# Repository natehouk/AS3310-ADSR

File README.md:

# SS-ADSR-1
Envelope generator based on the AS3310-ADSR.

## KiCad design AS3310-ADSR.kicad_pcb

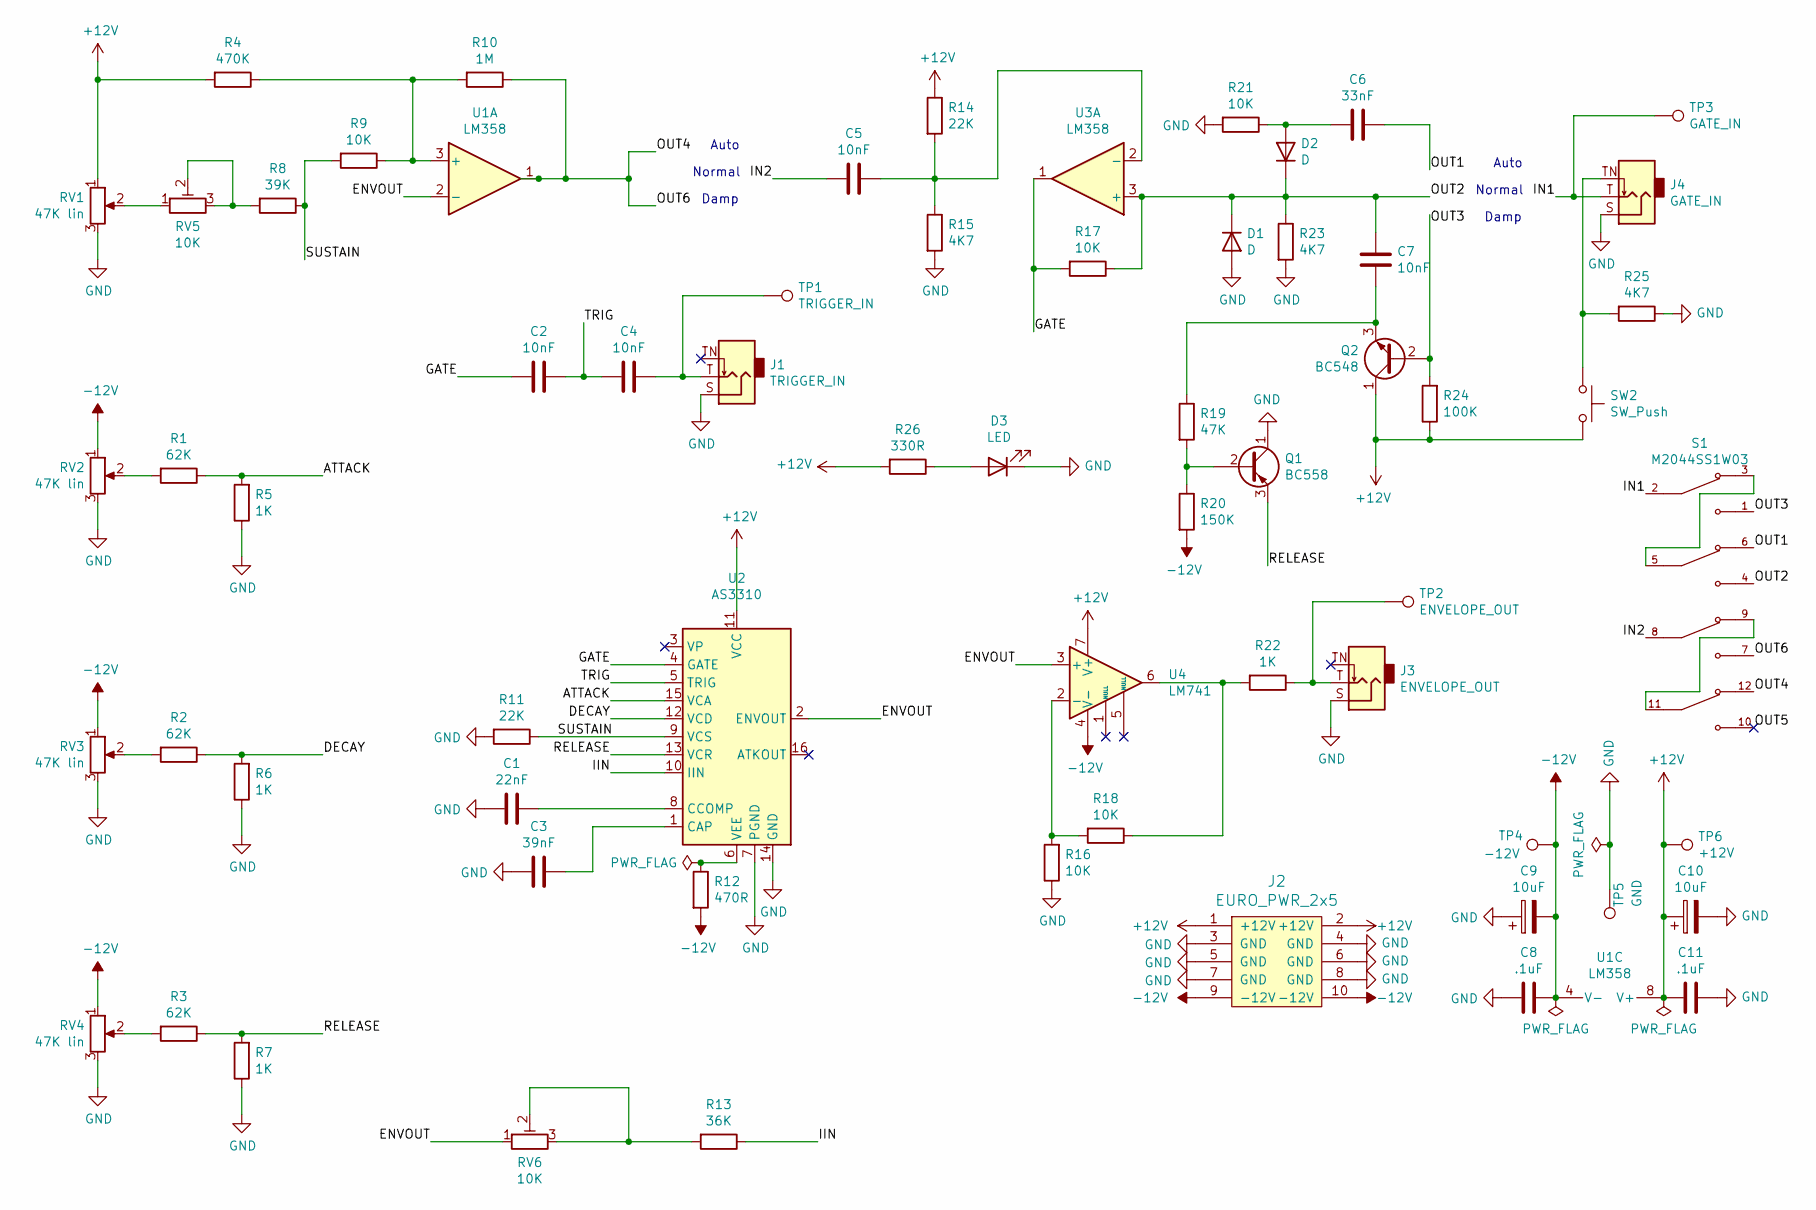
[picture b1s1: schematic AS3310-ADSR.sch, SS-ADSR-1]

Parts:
C1: 22nF; C_Disc_D7.5mm_W2.5mm_P5.00mm
C2, C4, C5, C7: 10nF; C_Disc_D7.5mm_W2.5mm_P5.00mm
C3: 39nF; C_Disc_D7.5mm_W2.5mm_P5.00mm
C6: 33nF; C_Disc_D7.5mm_W2.5mm_P5.00mm
C8, C11: .1uF; C_Disc_D7.5mm_W2.5mm_P5.00mm
C9, C10: 10uF; CP_Radial_D5.0mm_P2.50mm
D1, D2: D; D_DO-35_SOD27_P7.62mm_Horizontal
D3: LED; LED_D5.0mm
J1: TRIGGER_IN; Jack_3.5mm_QingPu_WQP-PJ398SM_Vertical_CircularHoles
J2: EURO_PWR_2x5; PinHeader_2x05_P2.54mm_Vertical
J3: ENVELOPE_OUT; Jack_3.5mm_QingPu_WQP-PJ398SM_Vertical_CircularHoles
J4: GATE_IN; Jack_3.5mm_QingPu_WQP-PJ398SM_Vertical_CircularHoles
Q1: BC558; TO-92_Inline
Q2: BC548; TO-92_Inline
R1, R2, R3: 62K; R_Axial_DIN0207_L6.3mm_D2.5mm_P10.16mm_Horizontal
R4: 470K; R_Axial_DIN0207_L6.3mm_D2.5mm_P10.16mm_Horizontal
R5, R6, R7, R22: 1K; R_Axial_DIN0207_L6.3mm_D2.5mm_P10.16mm_Horizontal
R8: 39K; R_Axial_DIN0207_L6.3mm_D2.5mm_P10.16mm_Horizontal
R9, R16, R17, R18, R21: 10K; R_Axial_DIN0207_L6.3mm_D2.5mm_P10.16mm_Horizontal
R10: 1M; R_Axial_DIN0207_L6.3mm_D2.5mm_P10.16mm_Horizontal
R11, R14: 22K; R_Axial_DIN0207_L6.3mm_D2.5mm_P10.16mm_Horizontal
R12: 470R; R_Axial_DIN0207_L6.3mm_D2.5mm_P10.16mm_Horizontal
R13: 36K; R_Axial_DIN0207_L6.3mm_D2.5mm_P10.16mm_Horizontal
R15, R23, R25: 4K7; R_Axial_DIN0207_L6.3mm_D2.5mm_P10.16mm_Horizontal
R19: 47K; R_Axial_DIN0207_L6.3mm_D2.5mm_P10.16mm_Horizontal
R20: 150K; R_Axial_DIN0207_L6.3mm_D2.5mm_P10.16mm_Horizontal
R24: 100K; R_Axial_DIN0207_L6.3mm_D2.5mm_P10.16mm_Horizontal
R26: 330R; R_Axial_DIN0207_L6.3mm_D2.5mm_P10.16mm_Horizontal
RV1, RV2, RV3, RV4: 47K lin; Potentiometer_Alpha_RD901F-40-00D_Single_Vertical
RV5, RV6: 10K; TRIM_3266W-1-102LF
S1: M2044SS1W03; SW_M2044SS1W03
SW2: SW_Push; SW_PS1024ALRED
TP1: TRIGGER_IN; TestPoint_Pad_4.0x4.0mm
TP2: ENVELOPE_OUT; TestPoint_Pad_4.0x4.0mm
TP3: GATE_IN; TestPoint_Pad_4.0x4.0mm
TP4: -12V; TestPoint_Pad_4.0x4.0mm
TP5: GND; TestPoint_Pad_4.0x4.0mm
TP6: +12V; TestPoint_Pad_4.0x4.0mm
U1, U3: LM358; DIP-8_W7.62mm
U2: AS3310; DIP-16_W7.62mm
U4: LM741; DIP-8_W7.62mm

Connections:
+12V: C10.1, C11.2, J2.1 (+12V), J2.2 (+12V), Q2.1 (C), R4.2, R14.1, R24.1, R26.2, RV1.1, SW2.2, TP6.1, U1.8 (V+), U2.11 (VCC), U4.7 (V+)
-12V: C8.1, C9.2, J2.9 (-12V), J2.10 (-12V), R12.2, R20.2, RV2.1, RV3.1, RV4.1, TP4.1, U1.4 (V-), U4.4 (V-)
/ATTACK: R1.1, R5.2, U2.15 (VCA)
/DECAY: R2.1, R6.2, U2.12 (VCD)
/ENVOUT: RV6.1, U1.2 (-), U2.2 (ENVOUT), U4.3 (+)
/GATE: C2.2, R17.2, U2.4 (GATE), U3.1
/IIN: R13.1, U2.10 (IIN)
/IN1: J4.T, S1.2, TP3.1
/IN2: C5.2, S1.8
/OUT1: C6.1, S1.6
/OUT2: C7.1, D1.1 (K), D2.1 (K), R17.1, R23.1, S1.4, U3.3 (+)
/OUT3: Q2.2 (B), R24.2, S1.1
/OUT4: R10.1, S1.7, S1.12, U1.1
/RELEASE: Q1.3 (E), R3.1, R7.2, U2.13 (VCR)
/SUSTAIN: R8.1, R9.2, R11.1, U2.9 (VCS)
/TRIG: C2.1, C4.2, U2.5 (TRIG)
GND: C1.2, C3.2, C8.2, C9.1, C10.2, C11.1, D1.2 (A), D3.1 (K), J1.S, J2.3 (GND), J2.4 (GND), J2.5 (GND), J2.6 (GND), J2.7 (GND), J2.8 (GND), J3.S, J4.S, Q1.1 (C), R5.1, R6.1, R7.1, R11.2, R15.2, R16.1, R21.2, R23.2, R25.1, RV1.3, RV2.3, RV3.3, RV4.3, TP5.1, U2.7 (PGND), U2.14 (GND)
unnamed: C1.1, U2.8 (CCOMP)
unnamed: C3.1, U2.1 (CAP)
unnamed: C4.1, J1.T, TP1.1
unnamed: C5.1, R14.2, R15.1, U3.2 (-)
unnamed: C6.2, D2.2 (A), R21.1
unnamed: C7.2, Q2.3 (E), R19.1
unnamed: D3.2 (A), R26.1
unnamed: J3.T, R22.1, TP2.1
unnamed: J4.TN, R25.2, SW2.1
unnamed: Q1.2 (B), R19.2, R20.1
unnamed: R1.2, RV2.2
unnamed: R2.2, RV3.2
unnamed: R3.2, RV4.2
unnamed: R8.2, RV5.2, RV5.3
unnamed: R4.1, R9.1, R10.2, U1.3 (+)
unnamed: R12.1, U2.6 (VEE)
unnamed: R13.2, RV6.2, RV6.3
unnamed: R16.2, R18.2, U4.2 (-)
unnamed: R18.1, R22.2, U4.6
unnamed: RV1.2, RV5.1
unnamed: S1.3, S1.5
unnamed: S1.9, S1.11

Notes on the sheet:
Auto
Normal
Damp

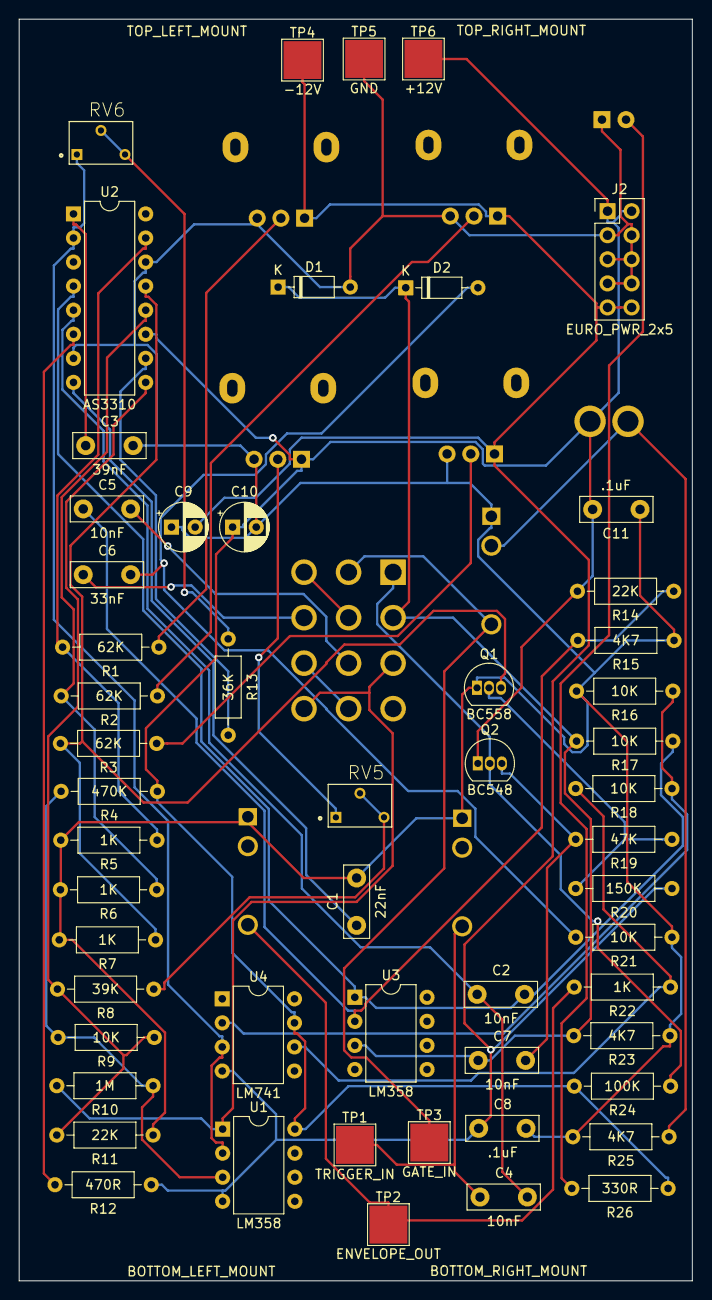
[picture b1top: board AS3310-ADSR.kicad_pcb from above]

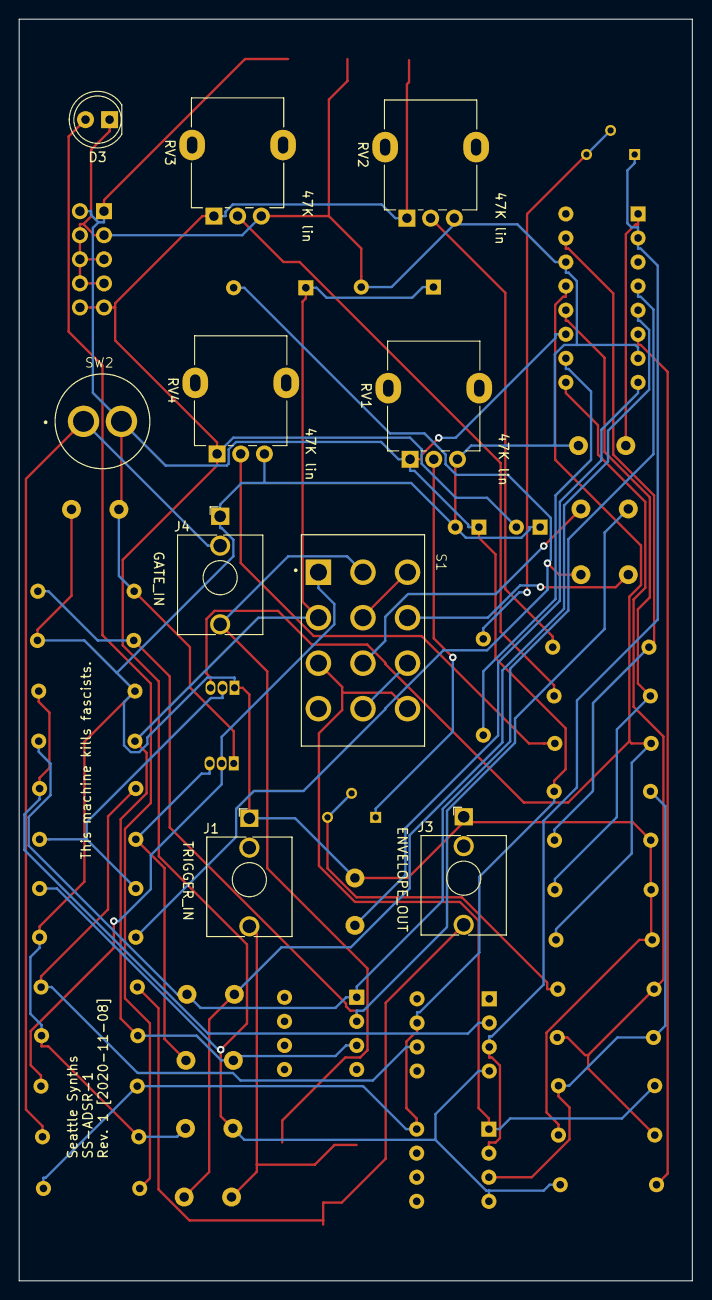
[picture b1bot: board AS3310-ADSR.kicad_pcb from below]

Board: 2 copper layers, 71.0 x 133.1 mm, 68 parts (10 on the bottom side), 39 nets.

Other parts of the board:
BOTTOM_LEFT_MOUNT: MountingHole_3.2mm_M3_Oval
BOTTOM_RIGHT_MOUNT: MountingHole_3.2mm_M3_Oval
TOP_LEFT_MOUNT: MountingHole_3.2mm_M3_Oval
TOP_RIGHT_MOUNT: MountingHole_3.2mm_M3_Oval

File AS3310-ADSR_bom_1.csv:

Component,Description,Part,References,Value,Footprint,Quantity Per PCB,Datasheet,Field4,Field5,Field6
1,Unpolarized capacitor,C,C2 C4 C5 C7,10nF,C_Disc_D7.5mm_W2.5mm_P5.00mm,4,~,,,
2,Unpolarized capacitor,C,C1,22nF,C_Disc_D7.5mm_W2.5mm_P5.00mm,1,~,,,
3,Unpolarized capacitor,C,C6,33nF,C_Disc_D7.5mm_W2.5mm_P5.00mm,1,~,,,
4,Unpolarized capacitor,C,C3,39nF,C_Disc_D7.5mm_W2.5mm_P5.00mm,1,~,,,
5,Unpolarized capacitor,C,C8 C11,.1uF,C_Disc_D7.5mm_W2.5mm_P5.00mm,2,~,,,
6,Unpolarized capacitor,C,C9 C10,10uF,C_Disc_D7.5mm_W2.5mm_P5.00mm,2,~,,,
7,Diode,D,D1 D2,D,D_DO-35_SOD27_P7.62mm_Horizontal,2,~,,,
8,Light emitting diode,LED,D3,LED,LED_D5.0mm,1,~,,,
9,,EURO_PWR_2x5,J2,EURO_PWR_2x5,PinHeader_2x05_P2.54mm_Vertical,1,,,,
10,"Audio Jack, 2 Poles (Mono / TS), Switched T Pole (Normalling)",AudioJack2_SwitchT,J1 J3 J4,TRIGGER_IN,Jack_3.5mm_QingPu_WQP-PJ398SM_Vertical_CircularHoles,3,~,,,
11,"0.1A Ic, 30V Vce, Small Signal NPN Transistor, TO-92",BC548,Q2,BC548,TO-92_Inline,1,https://www.onsemi.com/pub/Collateral/BC550-D.pdf,,,
12,"0.1A Ic, 30V Vce, PNP Small Signal Transistor, TO-92",BC558,Q1,BC558,TO-92_Inline,1,https://www.onsemi.com/pub/Collateral/BC556BTA-D.pdf,,,
13,Resistor,R,R26,330R,R_Axial_DIN0207_L6.3mm_D2.5mm_P10.16mm_Horizontal,1,~,,,
14,Resistor,R,R12,470R,R_Axial_DIN0207_L6.3mm_D2.5mm_P10.16mm_Horizontal,1,~,,,
15,Resistor,R,R5 R6 R7 R22,1K,R_Axial_DIN0207_L6.3mm_D2.5mm_P10.16mm_Horizontal,4,~,,,
16,Resistor,R,R15 R23 R25,4K7,R_Axial_DIN0207_L6.3mm_D2.5mm_P10.16mm_Horizontal,3,~,,,
17,Resistor,R,R9 R16 R17 R18 R21,10K,R_Axial_DIN0207_L6.3mm_D2.5mm_P10.16mm_Horizontal,5,~,,,
18,Resistor,R,R11 R14,22K,R_Axial_DIN0207_L6.3mm_D2.5mm_P10.16mm_Horizontal,2,~,,,
19,Resistor,R,R13,36K,R_Axial_DIN0207_L6.3mm_D2.5mm_P10.16mm_Horizontal,1,~,,,
20,Resistor,R,R8,39K,R_Axial_DIN0207_L6.3mm_D2.5mm_P10.16mm_Horizontal,1,~,,,
21,Resistor,R,R19,47K,R_Axial_DIN0207_L6.3mm_D2.5mm_P10.16mm_Horizontal,1,~,,,
22,Resistor,R,R1 R2 R3,62K,R_Axial_DIN0207_L6.3mm_D2.5mm_P10.16mm_Horizontal,3,~,,,
23,Resistor,R,R24,100K,R_Axial_DIN0207_L6.3mm_D2.5mm_P10.16mm_Horizontal,1,~,,,
24,Resistor,R,R20,150K,R_Axial_DIN0207_L6.3mm_D2.5mm_P10.16mm_Horizontal,1,~,,,
25,Resistor,R,R4,470K,R_Axial_DIN0207_L6.3mm_D2.5mm_P10.16mm_Horizontal,1,~,,,
26,Resistor,R,R10,1M,R_Axial_DIN0207_L6.3mm_D2.5mm_P10.16mm_Horizontal,1,~,,,
27,Trim-potentiometer,R_Potentiometer_Trim,RV5 RV6,10K,Potentiometer_Runtron_RM-065_Vertical,2,~,,,
28,Potentiometer,R_Potentiometer,RV1 RV2 RV3 RV4,47K lin,Potentiometer_Alpha_RD901F-40-00D_Single_Vertical,4,~,,,
29,,M2044SS1W03,S1,M2044SS1W03,SW_M2044SS1W03,1,30.9 mm,NKK Switches,5/9/18,Manufacturer Recommendations
30,"Push button switch, generic, two pins",SW_Push,SW2,SW_Push,SW_PUSH_6mm_H5mm,1,~,,,
31,"ADSR Voltage Controlled Envelope Generator, DIP-16/SOIC-16",AS3310,U2,AS3310,DIP-16_W7.62mm,1,http://www.alfarzpp.lv/eng/sc/AS3310.pdf,,,
32,"Low-Power, Dual Operational Amplifiers, DIP-8/SOIC-8/TO-99-8",LM358,U1 U3,LM358,DIP-8_W7.62mm,2,http://www.ti.com/lit/ds/symlink/lm2904-n.pdf,,,
33,"Operational Amplifier, DIP-8/TO-99-8",LM741,U4,LM741,DIP-8_W7.62mm,1,http://www.ti.com/lit/ds/symlink/lm741.pdf,,,





Component Groups:,33
Component Count:,58
Fitted Components:,58
Number of PCBs:,1
Total components:,58
Schematic Version:,1
Schematic Date:,2020-11-01
PCB Variant:,default
BoM Date:,Sun 08 Nov 2020 06:55:45 PM CET
Schematic Source:,AS3310-ADSR.sch
KiCad Version:,Eeschema 5.1.7

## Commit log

2020-11-01 Fix typo.
2020-11-01 Refactor
2020-11-02 Add Eurocad symbols and footprints.
2020-11-03 Refactor DP3T switch.
2020-11-08 Refacctor
